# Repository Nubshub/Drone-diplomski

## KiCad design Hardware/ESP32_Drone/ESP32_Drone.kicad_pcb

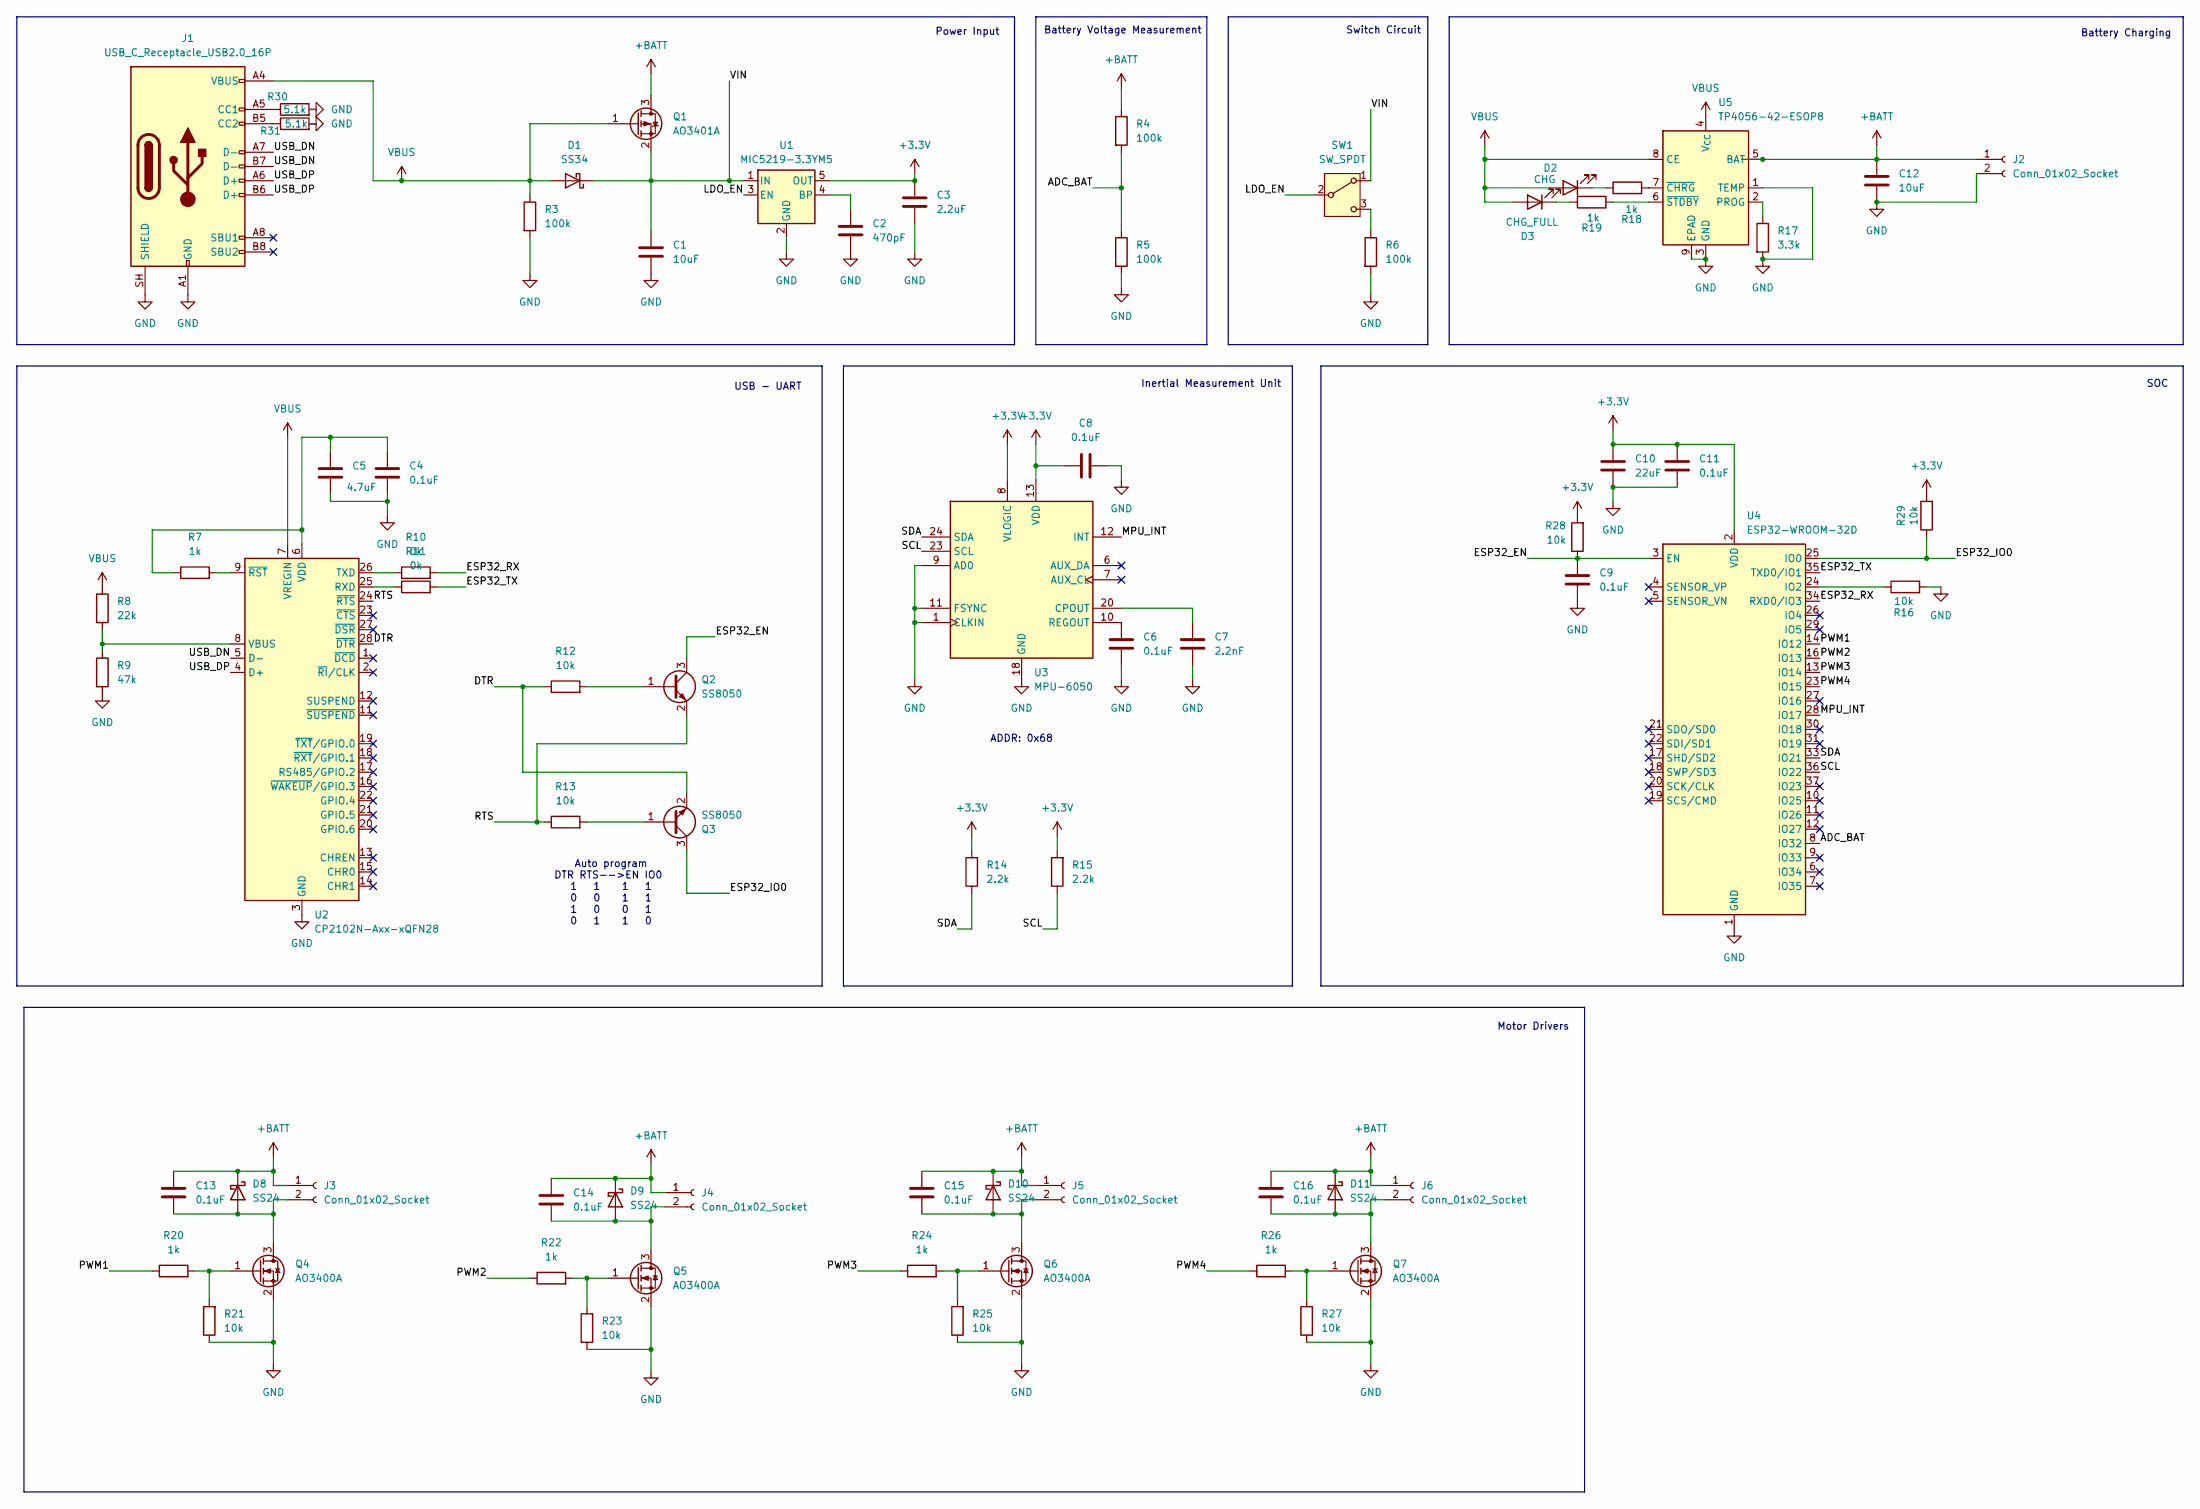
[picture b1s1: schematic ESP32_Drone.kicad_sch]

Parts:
C1, C12: 10uF; C_0805_2012Metric; LCSC C15850
C2: 470pF; C_0805_2012Metric; LCSC C1743
C3: 2.2uF; C_0805_2012Metric; LCSC C377773
C4, C6, C8, C9, C11, C13, C14, C15, C16: 0.1uF; C_0805_2012Metric; LCSC C49678
C5: 4.7uF; C_0805_2012Metric; LCSC C1779
C7: 2.2nF; C_0805_2012Metric; LCSC C28260
C10: 22uF; C_0805_2012Metric; LCSC C45783
D1: SS34; D_SMB; LCSC C8678
D2: CHG; LED_0603_1608Metric; LCSC C2286
D3: CHG_FULL; LED_0603_1608Metric; LCSC C2290
D8, D9, D10, D11: SS24; D_SMA; LCSC C50645
J1: USB_C_Receptacle_USB2.0_16P; USB_C_Receptacle_HRO_TYPE-C-31-M-12; LCSC C165948
J2: Conn_01x02_Socket; JST_PH_S2B-PH-K_1x02_P2.00mm_Horizontal; LCSC C173752
J3, J4, J5, J6: Conn_01x02_Socket; SolderWire-0.25sqmm_1x02_P4.2mm_D0.65mm_OD1.7mm
Q1: AO3401A; SOT-23; LCSC C15127
Q2, Q3: SS8050; SOT-23; LCSC C2150
Q4, Q5, Q6, Q7: AO3400A; SOT-23; LCSC C20917
R3, R4, R5, R6: 100k; R_0603_1608Metric; LCSC C25803
R7, R18, R19, R20, R22, R24, R26: 1k; R_0603_1608Metric; LCSC C21190
R8: 22k; R_0603_1608Metric; LCSC C31850
R9: 47k; R_0603_1608Metric; LCSC C25819
R10, R11: 0k; R_0603_1608Metric; LCSC C21189
R12, R13, R16, R21, R23, R25, R27, R28, R29: 10k; R_0603_1608Metric; LCSC C25804
R14, R15: 2.2k; R_0603_1608Metric; LCSC C4184
R17: 3.3k; R_0603_1608Metric; LCSC C22978
R30, R31: 5.1k; R_0603_1608Metric; LCSC C23186
SW1: SW_SPDT; SW_SPDT_CK_JS102011SAQN; LCSC C221660
U1: MIC5219-3.3YM5; SOT-23-5; LCSC C29613
U2: CP2102N-Axx-xQFN28; QFN-28-1EP_5x5mm_P0.5mm_EP3.35x3.35mm; LCSC C964632
U3: MPU-6050; InvenSense_QFN-24_4x4mm_P0.5mm; LCSC C24112
U4: ESP32-WROOM-32D; LCSC C473012
U5: TP4056-42-ESOP8; SOIC-8-1EP_3.9x4.9mm_P1.27mm_EP2.41x3.3mm_ThermalVias; LCSC C16581

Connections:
+3.3V: C3.1, C8.1, C10.1, C11.1, R14.2, R15.2, R28.2, R29.2, U1.5 (OUT), U3.8 (VLOGIC), U3.13 (VDD), U4.2 (VDD)
+BATT: C12.1, C13.1, C14.1, C15.1, C16.1, D8.1 (K), D9.1 (K), D10.1 (K), D11.1 (K), J2.1, J3.1, J4.1, J5.1, J6.1, Q1.3 (D), R4.1, U5.5 (BAT)
/ADC_BAT: R4.2, R5.1, U4.8 (IO32)
/DTR: Q3.2 (E), R12.1, U2.28 (~DTR)
/ESP32_EN: C9.1, Q2.3 (C), R28.1, U4.3 (EN)
/ESP32_IO0: Q3.3 (C), R29.1, U4.25 (IO0)
/ESP32_RX: R10.2, U4.34 (RXD0/IO3)
/ESP32_TX: R11.2, U4.35 (TXD0/IO1)
/LDO_EN: SW1.2 (B), U1.3 (EN)
/MPU_INT: U3.12 (INT), U4.28 (IO17)
/PWM1: R20.1, U4.14 (IO12)
/PWM2: R22.1, U4.16 (IO13)
/PWM3: R24.1, U4.13 (IO14)
/PWM4: R26.1, U4.23 (IO15)
/RTS: Q2.2 (E), R13.1, U2.24 (~RTS)
/SCL: R15.1, U3.23 (SCL), U4.36 (IO22)
/SDA: R14.1, U3.24 (SDA), U4.33 (IO21)
/USB_DN: J1.A7 (D-), J1.B7 (D-), U2.5 (D-)
/USB_DP: J1.A6 (D+), J1.B6 (D+), U2.4 (D+)
/VIN: C1.1, D1.1 (K), Q1.2 (S), SW1.1 (A), U1.1 (IN)
GND: C1.2, C2.2, C3.2, C4.2, C5.2, C6.2, C7.2, C8.2, C9.2, C10.2, C11.2, C12.2, J1.A1 (GND), J1.A12 (GND), J1.B1 (GND), J1.B12 (GND), J1.SH (SHIELD), J2.2, Q4.2 (S), Q5.2 (S), Q6.2 (S), Q7.2 (S), R3.2, R5.2, R6.2, R9.2, R16.2, R17.2, R21.1, R23.1, R25.1, R27.1, R30.2, R31.2, U1.2 (GND), U2.3 (GND), U2.29 (GND), U3.1 (CLKIN), U3.9 (AD0), U3.11 (FSYNC), U3.18 (GND), U4.1 (GND), U4.15 (GND), U4.38 (GND), U4.39 (GND), U5.1 (TEMP), U5.3 (GND), U5.9 (EPAD)
unnamed: D2.1 (K), R18.1
unnamed: D3.1 (K), R19.2
unnamed: C13.2, D8.2 (A), J3.2, Q4.3 (D)
unnamed: C14.2, D9.2 (A), J4.2, Q5.3 (D)
unnamed: C15.2, D10.2 (A), J5.2, Q6.3 (D)
unnamed: C16.2, D11.2 (A), J6.2, Q7.3 (D)
unnamed: J1.A5 (CC1), R30.1
unnamed: J1.B5 (CC2), R31.1
unnamed: Q2.1 (B), R12.2
unnamed: Q3.1 (B), R13.2
unnamed: Q4.1 (G), R20.2, R21.2
unnamed: Q5.1 (G), R22.2, R23.2
unnamed: Q6.1 (G), R24.2, R25.2
unnamed: Q7.1 (G), R26.2, R27.2
unnamed: R6.1, SW1.3 (C)
unnamed: C2.1, U1.4 (BP)
unnamed: R11.1, U2.25 (RXD)
unnamed: R10.1, U2.26 (TXD)
unnamed: R8.2, R9.1, U2.8 (VBUS)
unnamed: C4.1, C5.1, R7.1, U2.6 (VDD)
unnamed: R7.2, U2.9 (~RST)
unnamed: C7.1, U3.20 (CPOUT)
unnamed: C6.1, U3.10 (REGOUT)
unnamed: R16.1, U4.24 (IO2)
unnamed: R17.1, U5.2 (PROG)
unnamed: R18.2, U5.7 (~CHRG)
unnamed: R19.1, U5.6 (~STDBY)
VBUS: D1.2 (A), D2.2 (A), D3.2 (A), J1.A4 (VBUS), J1.A9 (VBUS), J1.B4 (VBUS), J1.B9 (VBUS), Q1.1 (G), R3.1, R8.1, U2.7 (VREGIN), U5.4 (V_{CC}), U5.8 (CE)

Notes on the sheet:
Motor Drivers
Switch Circuit
SOC
ADDR: 0x68
Inertial Measurement Unit
USB - UART
Battery Charging
Power Input
Battery Voltage Measurement
Auto program DTR RTS-->EN IO0 1 1 1 1 0 0 1 1 1 0 0 1 0 1 1 0

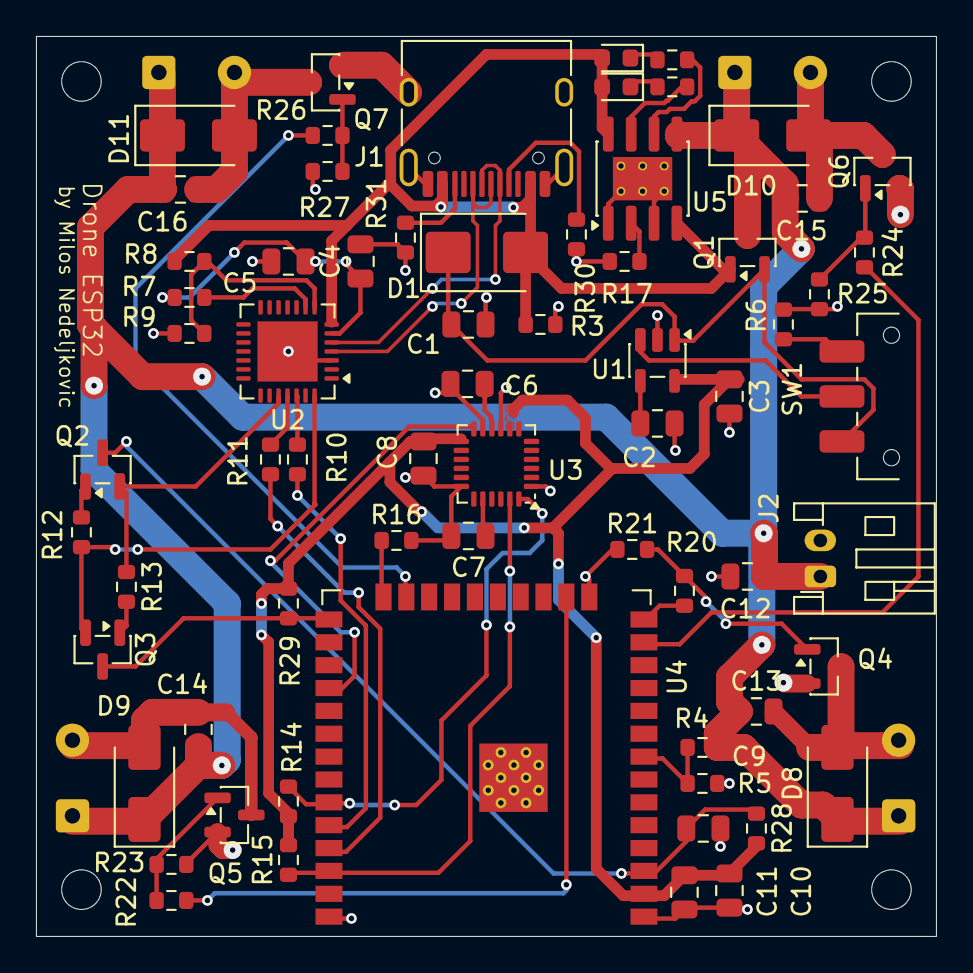
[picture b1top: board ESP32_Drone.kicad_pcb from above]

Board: 2 copper layers, 50.0 x 50.0 mm, 71 parts (0 on the bottom side), 49 nets.

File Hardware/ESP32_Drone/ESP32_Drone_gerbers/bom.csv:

Designator,Footprint,Quantity,Value,LCSC Part #
"C1, C12",0805,2,10uF,C15850
C10,0805,1,22uF,C45783
"C11, C13, C14, C15, C16, C4, C6, C8, C9",0805,9,0.1uF,C49678
C2,0805,1,470pF,C1740
C3,0805,1,2.2uF,C1806
C5,0805,1,4.7uF,C1822
C7,0805,1,2.2nF,C1653
D1,D_SMB,1,SS34,C8599
"D10, D11, D8, D9",D_SMA,4,SS24,C8598
D2,0603,1,CHG,C2286
D3,0603,1,CHG_FULL,C2297
J1,USB_C_Receptacle_HRO_TYPE-C-31-M-12,1,USB_C_Receptacle_USB2.0_16P,C165948
J2,JST_PH_S2B-PH-K_1x02_P2.00mm_Horizontal,1,Conn_01x02_Socket,C166021
"J3, J4, J5, J6",SolderWire-0.25sqmm_1x02_P4.2mm_D0.65mm_OD1.7mm,4,Conn_01x02_Socket,
Q1,SOT-23,1,AO3401A,C15127
"Q2, Q3",SOT-23,2,SS8050,C181090
"Q4, Q5, Q6, Q7",SOT-23,4,AO3400A,C20917
"R10, R11",0603,2,0k,C21189
"R12, R13, R16, R21, R23, R25, R27, R28, R29",0603,9,10k,C25804
"R14, R15",0603,2,2.2k,C4184
R17,0603,1,3.3k,C22978
"R18, R19",0603,2,1.3k,C4182
"R20, R22, R24, R26",0603,4,1k,C21190
"R3, R4, R5, R6",0603,4,100k,C25803
"R30, R31",0603,2,5.1k,C23186
R7,0603,1,1k,C22706
R8,0603,1,22k,C25879
R9,0603,1,47k,C25819
SW1,SW_SPDT_CK_JS102011SAQN,1,SW_SPDT,JS102011SAQN
U1,SOT-23-5,1,MIC5219-3.3YM5,C89366
U2,QFN-28-1EP_5x5mm_P0.5mm_EP3.35x3.35mm,1,CP2102N-Axx-xQFN28,C2652470
U3,InvenSense_QFN-24_4x4mm_P0.5mm,1,MPU-6050,C24112
U4,ESP32-WROOM-32D,1,ESP32-WROOM-32D,C473012
U5,SOIC-8-1EP_3.9x4.9mm_P1.27mm_EP2.41x3.3mm_ThermalVias,1,TP4056-42-ESOP8,C16581

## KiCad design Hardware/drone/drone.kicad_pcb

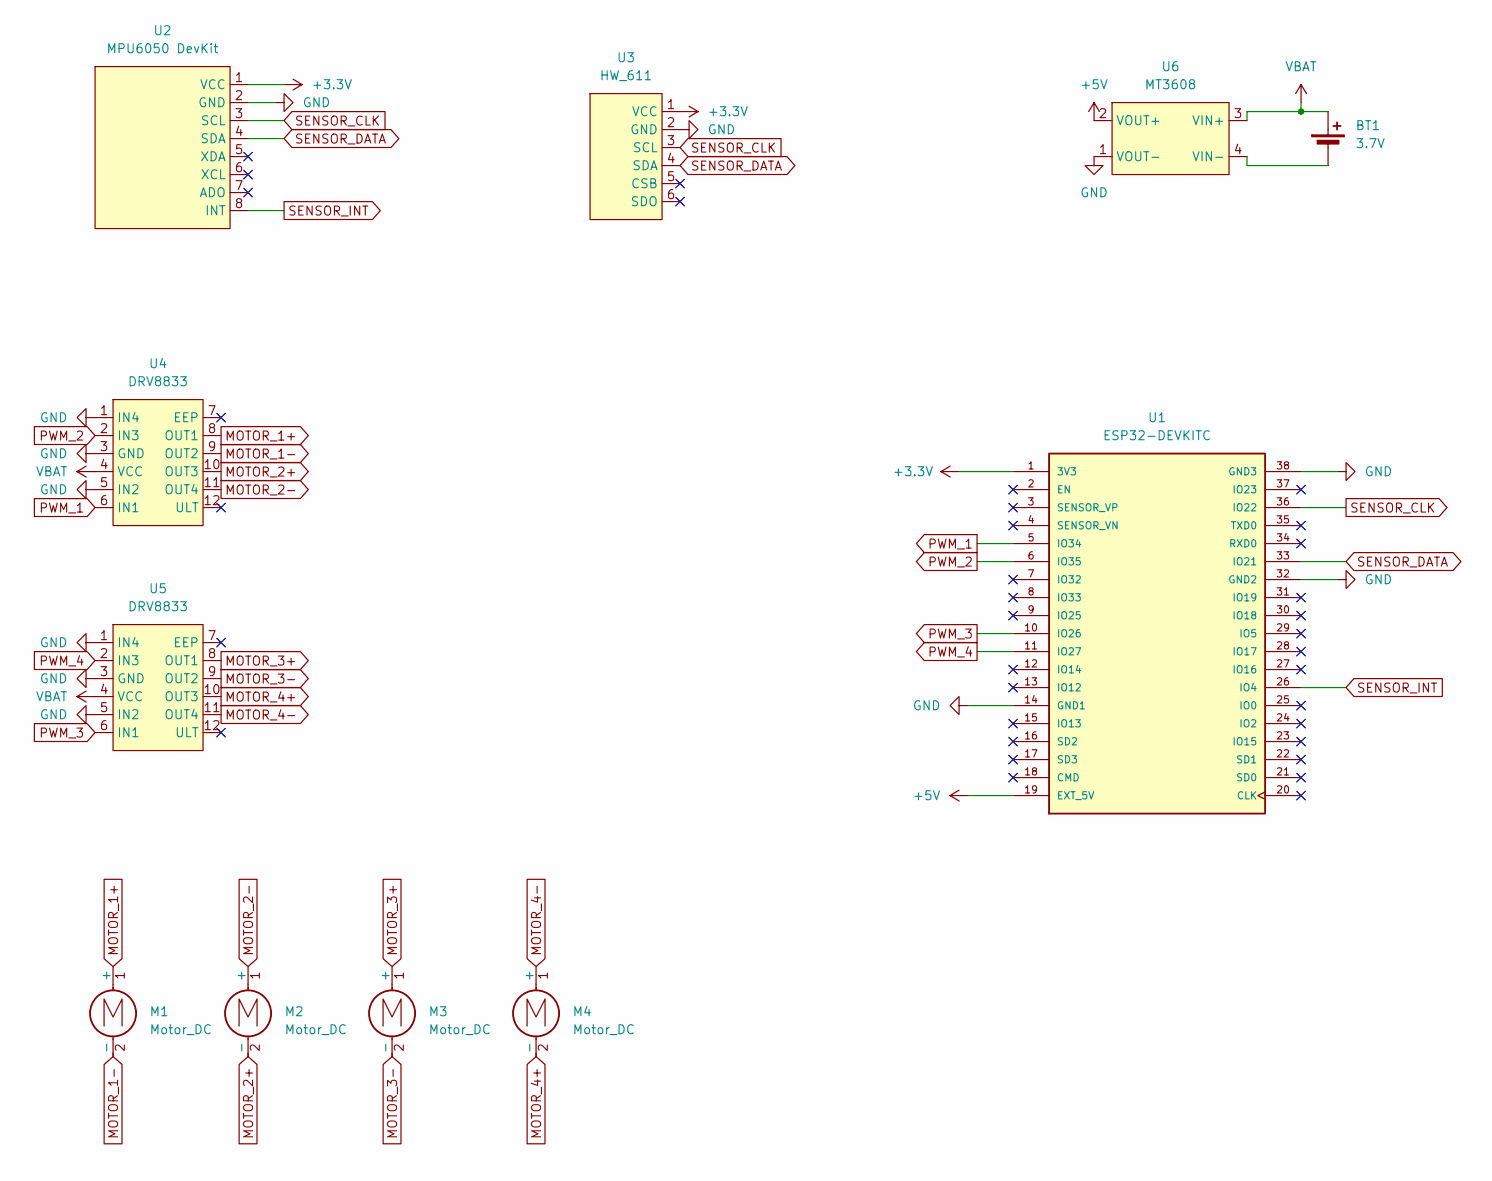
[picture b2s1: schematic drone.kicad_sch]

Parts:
BT1: 3.7V; PinHeader_1x02_P2.54mm_Vertical
M1, M2, M3, M4: Motor_DC; R_Axial_DIN0516_L15.5mm_D5.0mm_P5.08mm_Vertical
U1: ESP32-DEVKITC; ESP32-DevKitC; PARTREV N/A
U2: MPU6050 DevKit; module_mpu6050
U3: HW_611; module_bme280
U4, U5: DRV8833; DIP-12_W15.24mm_LongPads
U6: MT3608; hw-045

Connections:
+3.3V: U1.1 (3V3), U2.1 (VCC), U3.1 (VCC)
+5V: U1.19 (EXT_5V), U6.2 (VOUT+)
GND: U1.14 (GND1), U1.32 (GND2), U1.38 (GND3), U2.2 (GND), U3.2 (GND), U4.1 (IN4), U4.3 (GND), U4.5 (IN2), U5.1 (IN4), U5.3 (GND), U5.5 (IN2), U6.1 (VOUT-)
MOTOR_1+: M1.1 (+), U4.8 (OUT1)
MOTOR_1-: M1.2 (-), U4.9 (OUT2)
MOTOR_2+: M2.2 (-), U4.10 (OUT3)
MOTOR_2-: M2.1 (+), U4.11 (OUT4)
MOTOR_3+: M3.1 (+), U5.8 (OUT1)
MOTOR_3-: M3.2 (-), U5.9 (OUT2)
MOTOR_4+: M4.2 (-), U5.10 (OUT3)
MOTOR_4-: M4.1 (+), U5.11 (OUT4)
unnamed: BT1.2 (-), U6.4 (VIN-)
PWM_1: U1.5 (IO34), U4.6 (IN1)
PWM_2: U1.6 (IO35), U4.2 (IN3)
PWM_3: U1.10 (IO26), U5.6 (IN1)
PWM_4: U1.11 (IO27), U5.2 (IN3)
SENSOR_CLK: U1.36 (IO22), U2.3 (SCL), U3.3 (SCL)
SENSOR_DATA: U1.33 (IO21), U2.4 (SDA), U3.4 (SDA)
SENSOR_INT: U1.26 (IO4), U2.8 (INT)
VBAT: BT1.1 (+), U4.4 (VCC), U5.4 (VCC), U6.3 (VIN+)

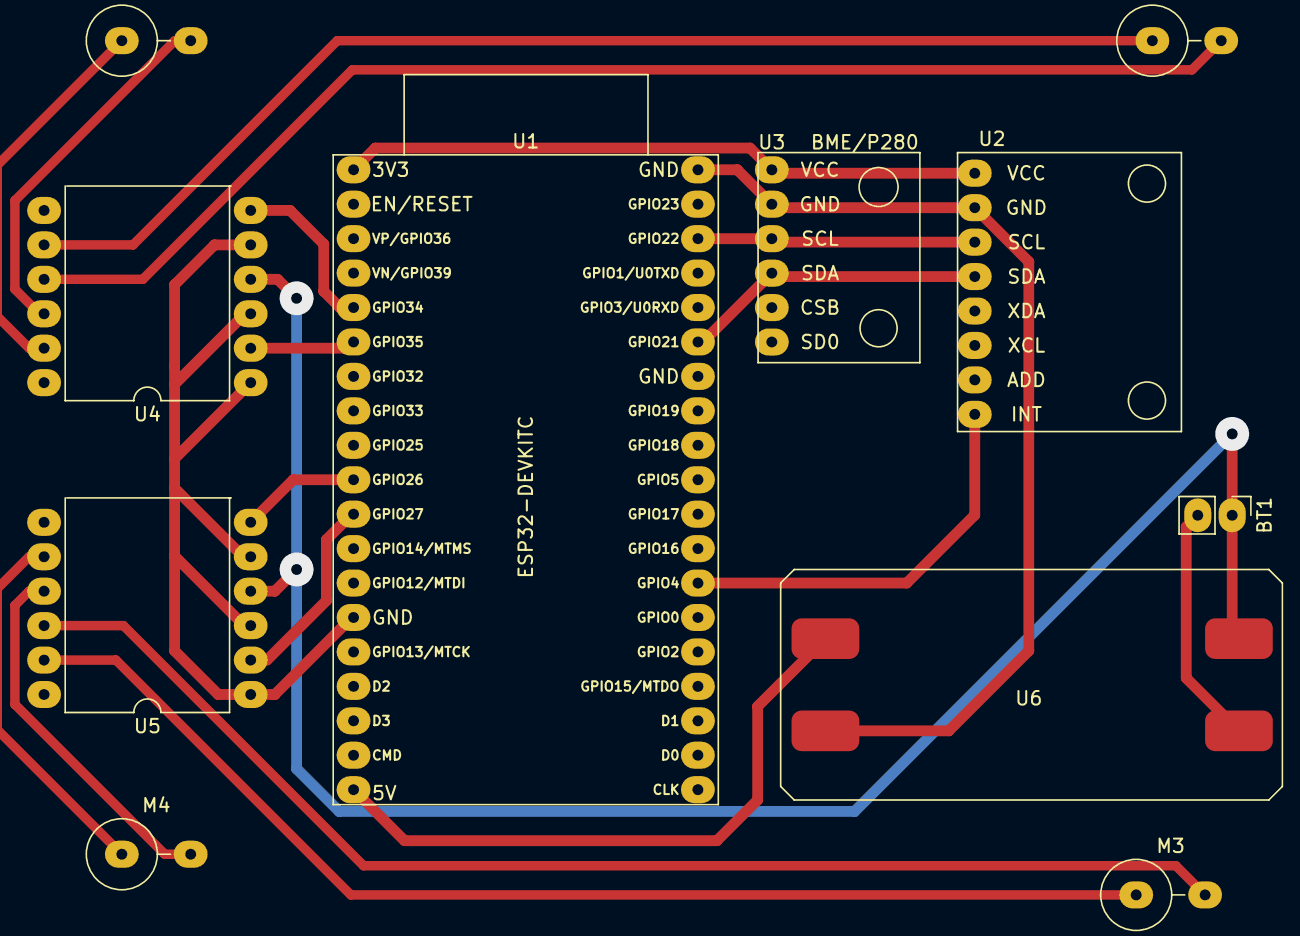
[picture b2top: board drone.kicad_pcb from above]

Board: 2 copper layers, 11 parts (0 on the bottom side), 20 nets.

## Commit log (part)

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2025-09-24 Init commit - MPU6050 Test
2025-09-24 Data sensor struct added.
2025-09-25 Interrupt pin configured for MPU-6050 sensor.
2025-09-25 Reorganize code structure (no functional changes).
2025-11-05 Code structure reorganized (no functional changes.)
2025-11-05 Wifi Access point created, UDP server.
2025-11-06 Parsing CRTP packets from Client (ESP Drone App).
2025-11-20 Hardware pinout added.
2025-11-20 Hardware pinout update.
2025-11-20 PWM configuration for DRV8833 and DC motor.
2025-11-27 PWM tuning.
2026-01-18 Hardware schematic update.
2026-02-25 Footprints updated.
2026-02-27 PCB design v1.0
2026-05-11 New hardware schematic.
2026-05-12 JCSC field added.
2026-05-13 PCB layout v1.0
2026-05-15 JCSC numbers updated.
2026-05-26 Fixed charger LEDs.
2026-05-27 PWM thrust for all motors.
2026-05-27 MPU6050 calibration.
2026-05-27 Thurst error correction
2026-06-27 Test version of PID control algorithm.
2026-06-27 PID calibration
2026-06-28 New code structure
